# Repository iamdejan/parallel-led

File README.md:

# Parallel LED

This is my first project using [KiCAD](https://www.kicad.org/), as I tried to find a hobby outside of programming.

## How to Use

Open `parallel-led.kicad_pro` with KiCAD.

NOTE: I created this project with KiCAD v7.0.6, so please check for compatibility with your KiCAD.

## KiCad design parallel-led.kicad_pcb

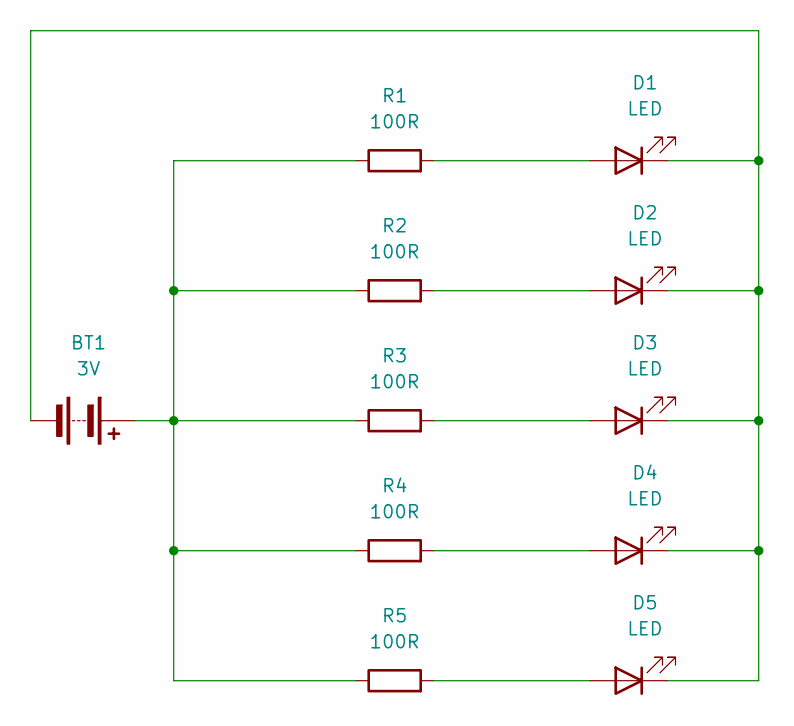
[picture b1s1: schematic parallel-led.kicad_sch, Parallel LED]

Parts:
BT1: 3V; TerminalBlock_Altech_AK300-2_P5.00mm
D1, D2, D3, D4, D5: LED; BeginnerLED_D5.0mm
R1, R2, R3, R4, R5: 100R; R_Axial_DIN0207_L6.3mm_D2.5mm_P10.16mm_Horizontal

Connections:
unnamed: BT1.1 (+), R1.1, R2.1, R3.1, R4.1, R5.1
unnamed: BT1.2 (-), D1.1 (K), D2.1 (K), D3.1 (K), D4.1 (K), D5.1 (K)
unnamed: D1.2 (A), R1.2
unnamed: D2.2 (A), R2.2
unnamed: D3.2 (A), R3.2
unnamed: D4.2 (A), R4.2
unnamed: D5.2 (A), R5.2

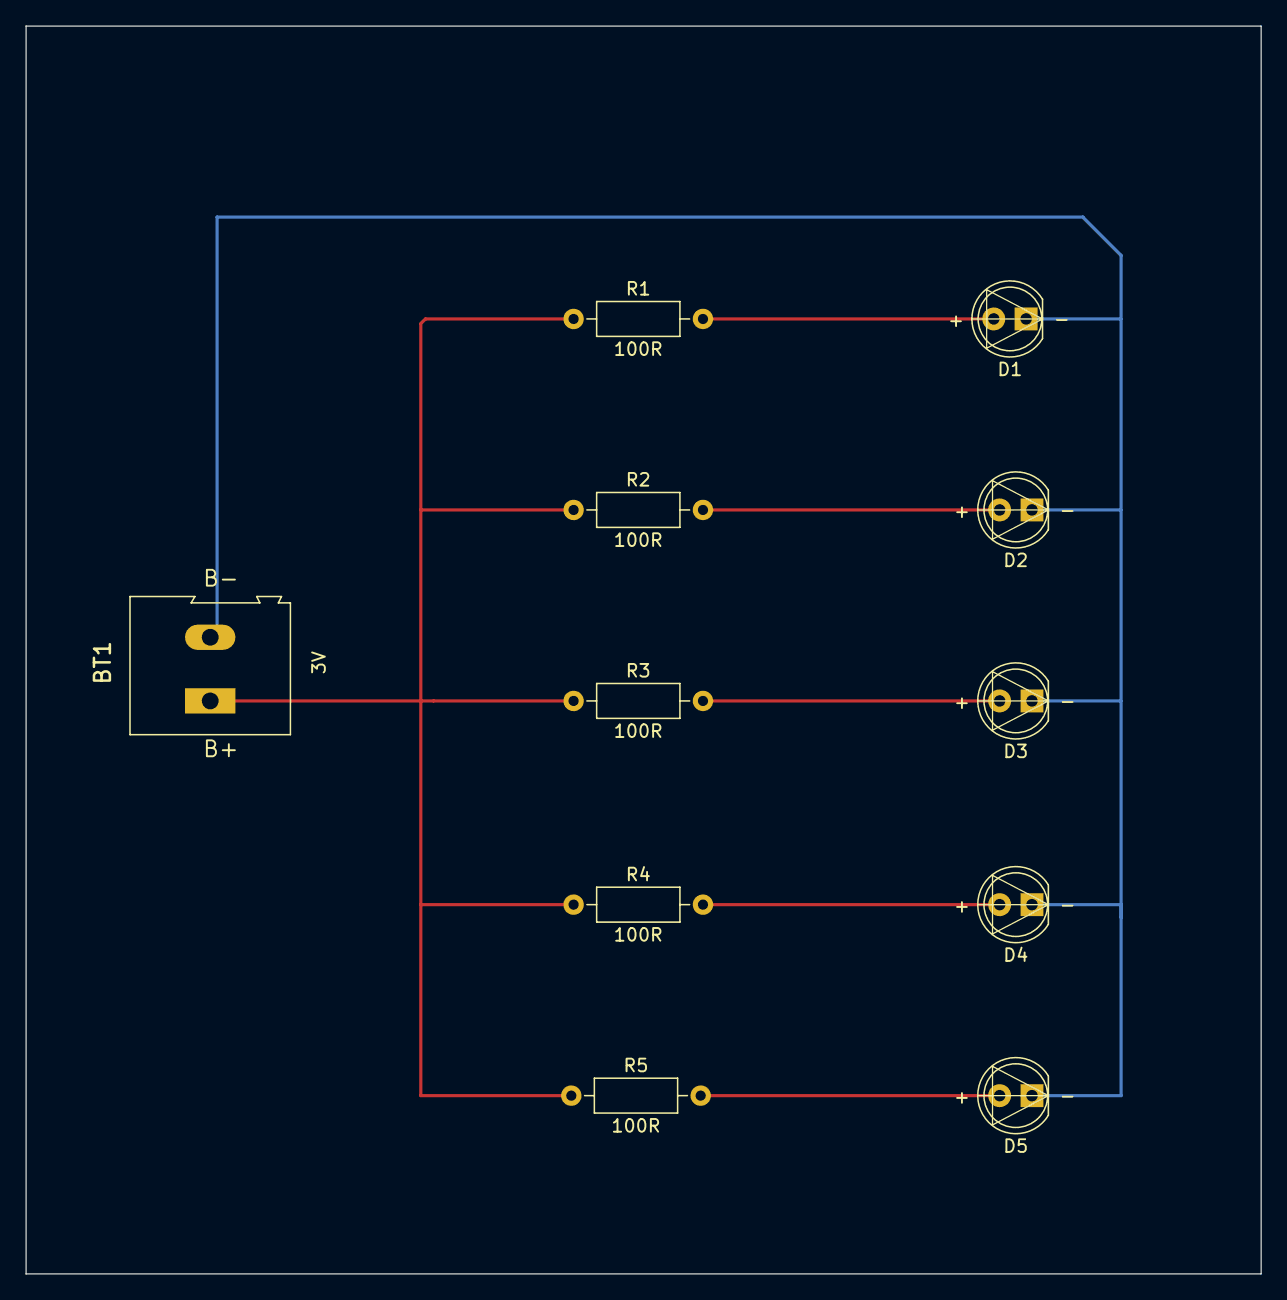
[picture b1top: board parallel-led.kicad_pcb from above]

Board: 2 copper layers, 97.0 x 98.0 mm, 11 parts (0 on the bottom side), 7 nets.

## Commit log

2023-08-03 add schematic
2023-08-03 fix components' footprint
2023-08-03 add license and readme
2023-08-05 refining pcb design
2023-08-05 change license
2023-08-05 add + - sign for each led
2023-08-05 remove lockfile
2023-08-05 modify D1; modify battery
2023-08-05 unhide
2023-08-05 replace led with custom footprint
2023-08-05 feat: create new footprint to add + and - sign to LED (#1)
2023-08-06 change drillshape
2023-08-06 fix: sign in custom led footprint
2023-08-07 fix: polarity sign on all LEDs
